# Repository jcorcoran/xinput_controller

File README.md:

# xinput_controller

## Installation

Getting the xinput libraries working is a bit of a process.
Last tested with the following software baslines:
  - Teensyduino 1.50: https://www.pjrc.com/teensy/td_150/TeensyduinoInstall.exe
  - Arduino 1.8.11: https://www.arduino.cc/en/main/OldSoftwareReleases
  - ArduinoXInput_Teensy 1.0.6: https://github.com/dmadison/ArduinoXInput_Teensy/releases
  - ArduinoXInput v1.2.1: https://github.com/dmadison/ArduinoXInput  (installable through ARduino Tools > Manage Libraries)
 
Follow the installation instructions for ArduinoXInput library found [in its repo](https://github.com/dmadison/ArduinoXInput_Teensy)

## PCB

* KiCAD project files and gerbers are [here](https://github.com/jcorcoran/xinput_controller/tree/master/pcb/galvanize)
* Also available for easy one-click ordering from: https://oshpark.com/shared_projects/lwcYD8mQ

Generic breakout board for a typical xinput device that provides the following on 0.1" pitch headers:
   * 10x discrete button input channels
   * 4x discrete D-Pad inputs (Up, Down, Left, Right)
   * 6x analog input channels (Right Axis X & Y, Left Axis X & Y, Left & Right Triggers)

### Bill of materials:

  * 1x - Teensy LC
  * 2x - 1x14 0.1" pitch female pin headers
  * 14x - 1x2 0.1" pitch male pin headers
  * 6x - 1x3 0.1" pitch male pin headers
  * C1, C2, C3 filter caps are optional

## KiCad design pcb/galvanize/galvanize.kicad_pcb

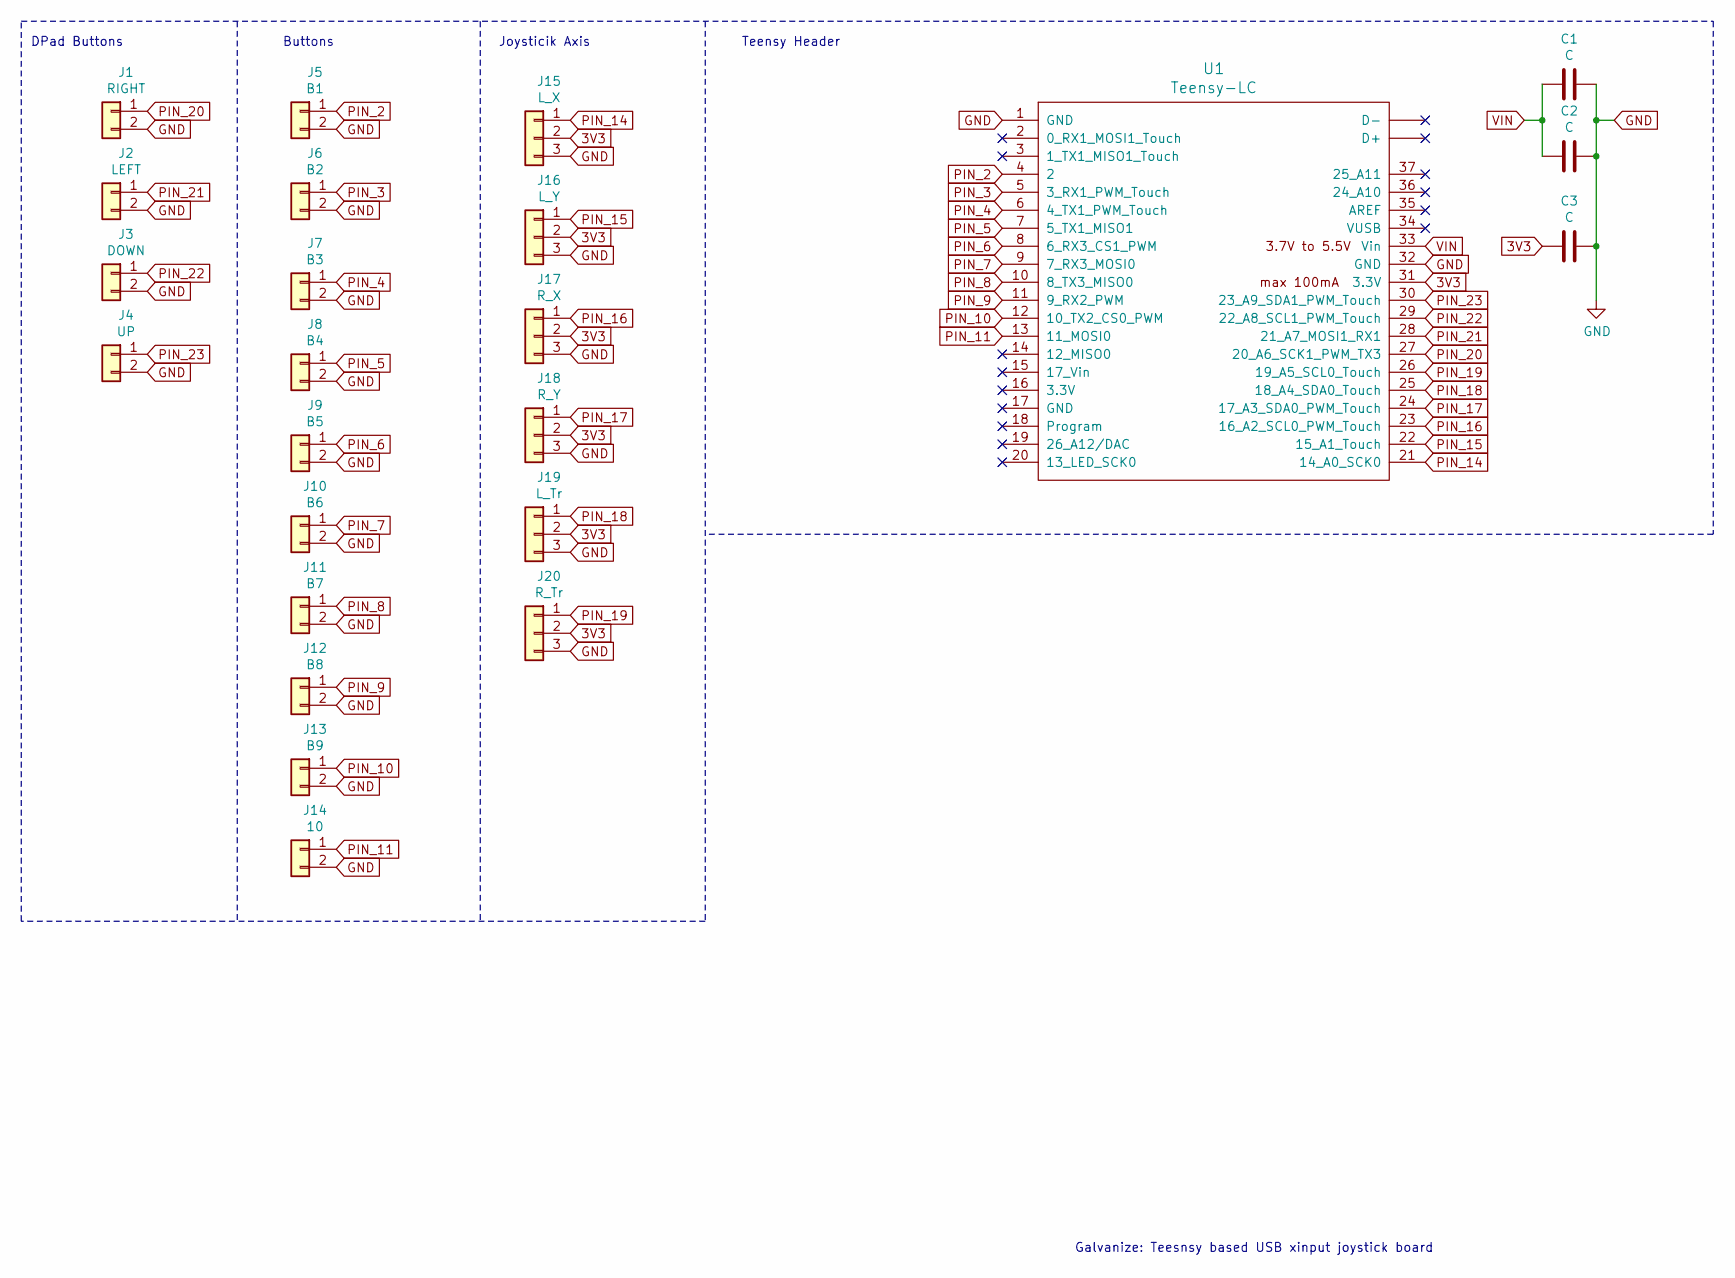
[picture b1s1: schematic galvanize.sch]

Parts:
C1, C2, C3: C; C_0805_2012Metric_Pad1.15x1.40mm_HandSolder
J1: RIGHT; PinHeader_1x02_P2.54mm_Vertical_Labeled
J2: LEFT; PinHeader_1x02_P2.54mm_Vertical_Labeled
J3: DOWN; PinHeader_1x02_P2.54mm_Vertical_Labeled
J4: UP; PinHeader_1x02_P2.54mm_Vertical_Labeled
J5: B1; PinHeader_1x02_P2.54mm_Vertical_Labeled
J6: B2; PinHeader_1x02_P2.54mm_Vertical_Labeled
J7: B3; PinHeader_1x02_P2.54mm_Vertical_Labeled
J8: B4; PinHeader_1x02_P2.54mm_Vertical_Labeled
J9: B5; PinHeader_1x02_P2.54mm_Vertical_Labeled
J10: B6; PinHeader_1x02_P2.54mm_Vertical_Labeled
J11: B7; PinHeader_1x02_P2.54mm_Vertical_Labeled
J12: B8; PinHeader_1x02_P2.54mm_Vertical_Labeled
J13: B9; PinHeader_1x02_P2.54mm_Vertical_Labeled
J14: 10; PinHeader_1x02_P2.54mm_Vertical_Labeled
J15: L_X; PinHeader_1x03_P2.54mm_Vertical_Labeled
J16: L_Y; PinHeader_1x03_P2.54mm_Vertical_Labeled
J17: R_X; PinHeader_1x03_P2.54mm_Vertical_Labeled
J18: R_Y; PinHeader_1x03_P2.54mm_Vertical_Labeled
J19: L_Tr; PinHeader_1x03_P2.54mm_Vertical_Labeled
J20: R_Tr; PinHeader_1x03_P2.54mm_Vertical_Labeled
U1: Teensy-LC; Teensy30_31_32_LC

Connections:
3V3: C3.2, J15.2, J16.2, J17.2, J18.2, J19.2, J20.2, U1.31 (3.3V)
GND: C1.1, C2.1, C3.1, J1.2, J2.2, J3.2, J4.2, J5.2, J6.2, J7.2, J8.2, J9.2, J10.2, J11.2, J12.2, J13.2, J14.2, J15.3, J16.3, J17.3, J18.3, J19.3, J20.3, U1.1 (GND), U1.32 (GND)
PIN_2: J5.1, U1.4 (2)
PIN_3: J6.1, U1.5 (3_RX1_PWM_Touch)
PIN_4: J7.1, U1.6 (4_TX1_PWM_Touch)
PIN_5: J8.1, U1.7 (5_TX1_MISO1)
PIN_6: J9.1, U1.8 (6_RX3_CS1_PWM)
PIN_7: J10.1, U1.9 (7_RX3_MOSI0)
PIN_8: J11.1, U1.10 (8_TX3_MISO0)
PIN_9: J12.1, U1.11 (9_RX2_PWM)
PIN_10: J13.1, U1.12 (10_TX2_CS0_PWM)
PIN_11: J14.1, U1.13 (11_MOSI0)
PIN_14: J15.1, U1.21 (14_A0_SCK0)
PIN_15: J16.1, U1.22 (15_A1_Touch)
PIN_16: J17.1, U1.23 (16_A2_SCL0_PWM_Touch)
PIN_17: J18.1, U1.24 (17_A3_SDA0_PWM_Touch)
PIN_18: J19.1, U1.25 (18_A4_SDA0_Touch)
PIN_19: J20.1, U1.26 (19_A5_SCL0_Touch)
PIN_20: J1.1, U1.27 (20_A6_SCK1_PWM_TX3)
PIN_21: J2.1, U1.28 (21_A7_MOSI1_RX1)
PIN_22: J3.1, U1.29 (22_A8_SCL1_PWM_Touch)
PIN_23: J4.1, U1.30 (23_A9_SDA1_PWM_Touch)
VIN: C1.2, C2.2, U1.33 (Vin)

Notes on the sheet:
DPad Buttons
Buttons
Joysticik Axis
Teensy Header
Galvanize: Teesnsy based USB xinput joystick board

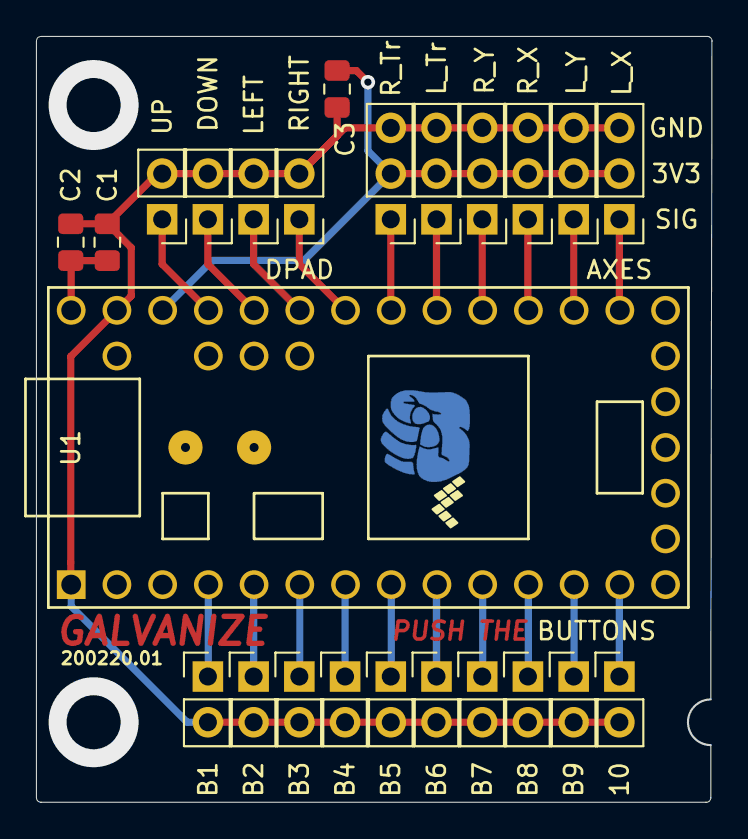
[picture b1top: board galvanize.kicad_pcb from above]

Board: 2 copper layers, 37.5 x 42.5 mm, 24 parts (0 on the bottom side), 23 nets.

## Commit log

2019-03-05 Create xinput.cpp
    Removed "SOCD cleaner" feature which prevents hitting multiple DPAD values simultaneously.
    Don't filter the DPAD values at all on the controller end
    https://github.com/dmadison/MSF-XINPUT/commit/a636230b351761e78916faf3afa97afc56bffac0#diff-51fc4996ee98979fe9656f9023771880
2019-03-05 Create xinput_controller.ino
    initial commit
2019-03-06 Update xinput_controller.ino
    Add L3 and R3 buttons.
    Add axis
    Map buttons so pin increases with order on smart dashboard.
2020-02-18 Initial commit of PCB files.
2020-02-20 Add pcb files to repo.
2020-02-24 Add PCB and code updates for prelim release. Buttons and two axes tested working on TeensyLC.
2020-03-06 Update xinput_controller.ino
    Modify to disable unused joystick channels
2021-09-28 Add PCB notes
2021-09-28 add pcb image
2021-09-28 fix formatting
